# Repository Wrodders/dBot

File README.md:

# Two Wheel Self Balancing Mobile Robot

Final Year Capstone Mechatronics Project. 
Designed to be a cost effective platform for research and development of autonomous 
mobile robotics. The non linear and unstable dynamics of the Two Wheel Self Balancing Mobile Robot (TWSBMR)
make it a challenging platform for control and navigation.

Low Level motor control implemented on STM32F411RE microcontroller, using LibOpenCM3.
High Level Monocular Navigation uses RaspberryPi 5 with the Pi Camera V3.
[ComsTerm](https://github.com/Wrodders/ComsTerm) used as engineering UI. 

## Design

The project was built around milestones of autonomy:

* Stabilization
* Positional Control
* Teleoperation
* Path Following 
* Path Recovery 
* Track Racing

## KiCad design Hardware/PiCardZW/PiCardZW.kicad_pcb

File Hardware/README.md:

# STM32 Black Pill Connection Diagram

```mermaid
graph TB
  subgraph STM32F401
    USART2 -->|PA2/3| Debug/Prog
    USART1 -->|PB6/7| Bluetooth
    TIMER3 -->|PA6/7 PB0/1| PWM
    TIMER1 -->|PA8/9/10/11| Encoder
    I2C1 --> |PB8/9| MPU6050
  end
```

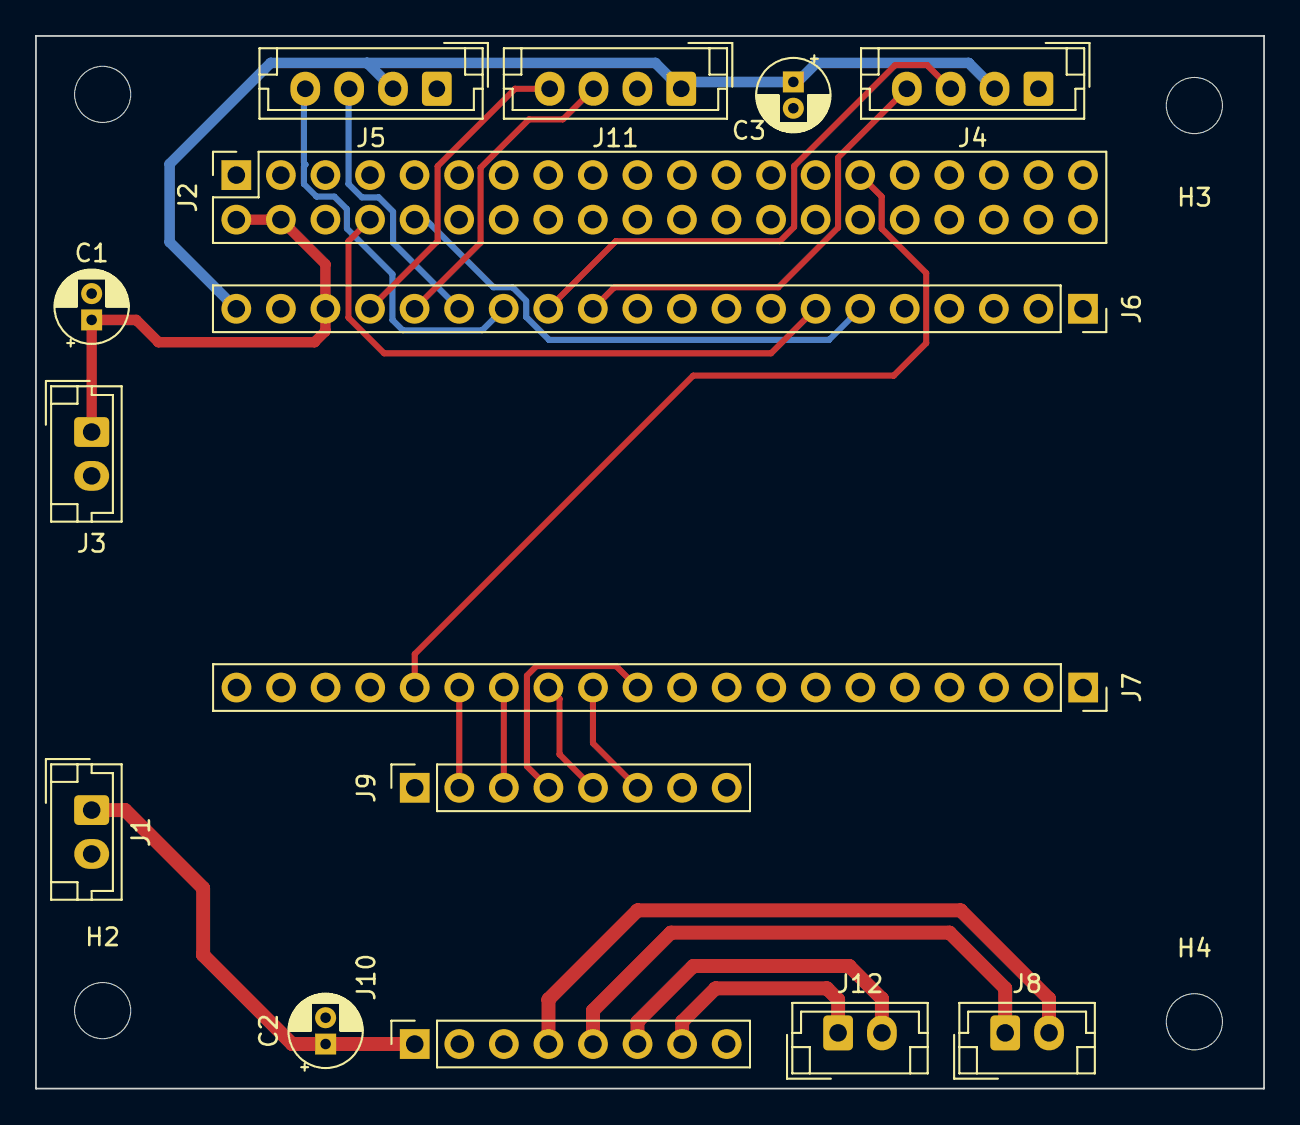
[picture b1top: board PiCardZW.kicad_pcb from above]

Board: 2 copper layers, 70.0 x 60.0 mm, 19 parts (0 on the bottom side), 22 nets.

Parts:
C1, C3: 10u; CP_Radial_D4.0mm_P1.50mm
C2: 100u; CP_Radial_D4.0mm_P1.50mm
H1, H2, H3, H4: MountingHole; MountingHole_3.2mm_M3
J1, J8, J12: Screw_Terminal_01x02; JST_EH_B2B-EH-A_1x02_P2.50mm_Vertical
J2: Conn_02x20_Odd_Even; PinSocket_2x20_P2.54mm_Vertical
J3: Conn_01x02; JST_EH_B2B-EH-A_1x02_P2.50mm_Vertical
J4, J5, J11: Conn_01x04; JST_EH_B4B-EH-A_1x04_P2.50mm_Vertical
J6, J7: Conn_01x20; PinSocket_1x20_P2.54mm_Vertical
J9, J10: Conn_01x08; PinSocket_1x08_P2.54mm_Vertical

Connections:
+3.3V: C3.1, J4.2, J5.2, J6.20, J7.3, J11.1
+5V: C1.1, J2.2, J2.4, J3.1, J6.18, J7.1
AOUT1: J8.2, J10.4
AOUT2: J8.1, J10.5
BOUT1: J10.6, J12.2
BOUT2: J10.7, J12.1
DEBUG_RX: J2.8, J6.7
DEBUG_TX: J2.10, J6.6
DRV_EN: J7.11, J9.4
ENCL_A: J4.4, J6.12
ENCL_B: J4.3, J6.13
ENCR_A: J5.4, J6.14
ENCR_B: J5.3, J6.15
GND: C1.2, C2.2, C3.2, J1.2, J2.6, J2.9, J2.14, J2.20, J2.25, J2.30, J2.34, J2.39, J3.2, J4.1, J5.1, J6.19, J7.2, J9.8, J10.3, J10.8, J11.2
IMU_SCL: J6.16, J11.3
IMU_SDA: J6.17, J11.4
ML_PWMA: J7.15, J9.2
ML_PWMB: J7.14, J9.3
MR_PWMA: J7.13, J9.5
MR_PWMB: J7.12, J9.6
VM: C2.1, J1.1, J10.1
nRST: J2.29, J7.16

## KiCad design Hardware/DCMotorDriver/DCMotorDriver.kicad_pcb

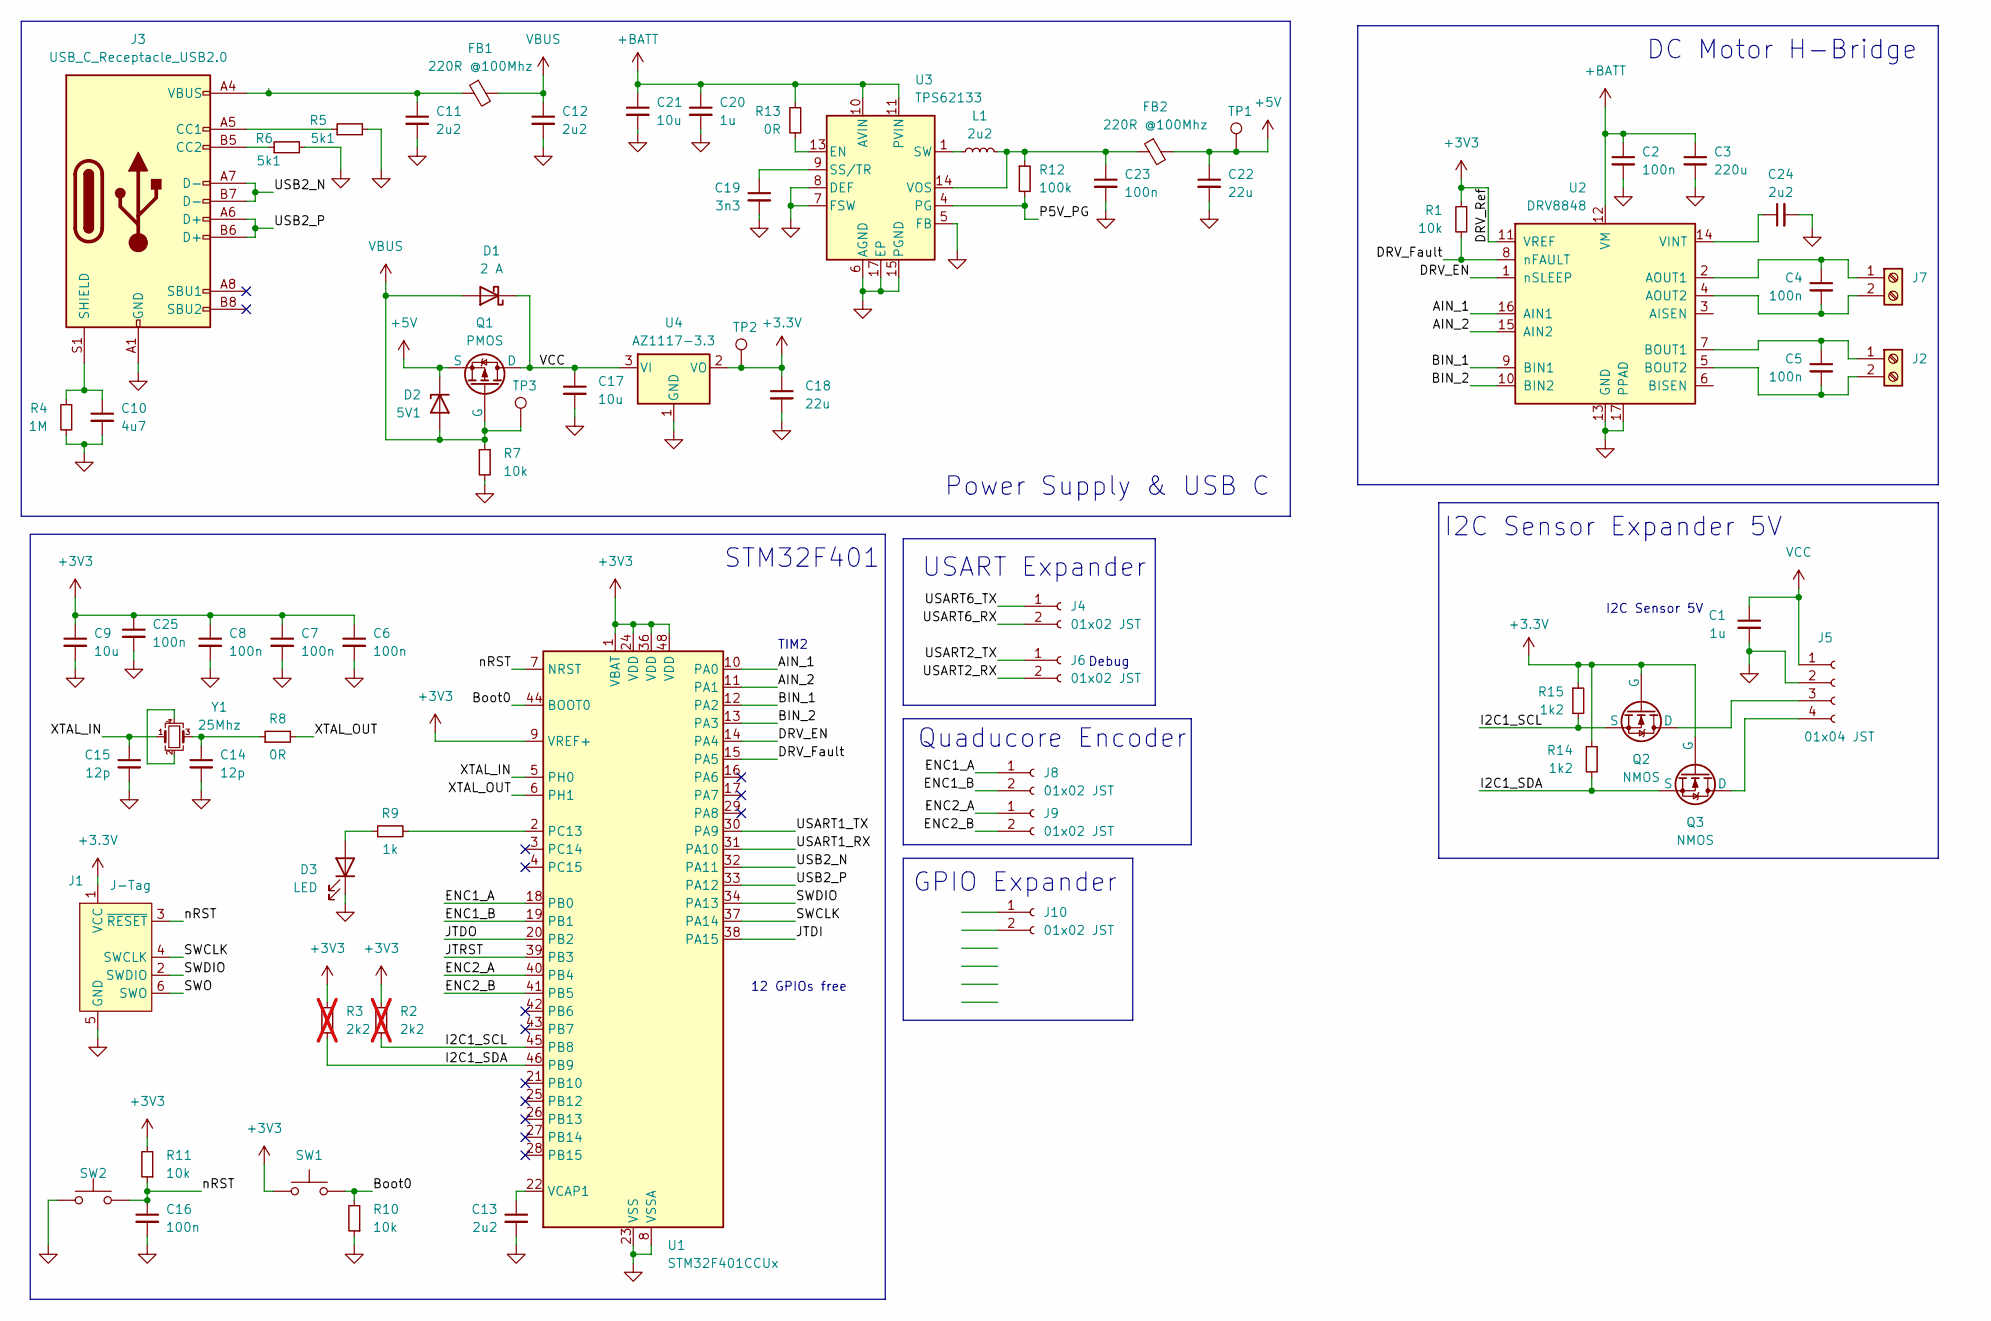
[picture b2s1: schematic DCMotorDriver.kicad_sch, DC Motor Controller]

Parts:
C1, C20: 1u; C_0402_1005Metric
C2, C4, C5, C6, C7, C8, C16, C23, C25: 100n; C_0402_1005Metric
C3: 220u; C_0402_1005Metric
C9, C17, C21: 10u; C_0402_1005Metric
C10: 4u7; C_0402_1005Metric
C11, C12, C13, C24: 2u2; C_0402_1005Metric
C14, C15: 12p; C_0402_1005Metric
C18, C22: 22u; C_0402_1005Metric
C19: 3n3; C_0402_1005Metric
D1: 2 A; D_0603_1608Metric
D2: 5V1; D_0402_1005Metric
D3: LED; D_0402_1005Metric
FB1, FB2: 220R @100Mhz; L_0402_1005Metric
J1: J-Tag; Tag-Connect_TC2030-IDC-FP_2x03_P1.27mm_Vertical
J2, J7: Screw_Terminal_01x02; PinHeader_1x02_P2.54mm_Horizontal
J3: USB_C_Receptacle_USB2.0; USB_C_Receptacle_XKB_U262-16XN-4BVC11
J4, J6, J8, J9, J10: 01x02 JST; JST_EH_B2B-EH-A_1x02_P2.50mm_Vertical
J5: 01x04 JST; JST_EH_B4B-EH-A_1x04_P2.50mm_Vertical
L1: 2u2; L_0805_2012Metric
Q1: PMOS; SOT-23-3
Q2, Q3: NMOS; SOT-23-3
R1, R7, R10, R11: 10k; R_0402_1005Metric
R2, R3: 2k2; R_0402_1005Metric; not fitted
R4: 1M; R_0402_1005Metric
R5, R6: 5k1; R_0402_1005Metric
R8, R13: 0R; R_0402_1005Metric
R9: 1k; R_0402_1005Metric
R12: 100k; R_0402_1005Metric
R14, R15: 1k2; R_0402_1005Metric
SW1, SW2: SW_Push; SW_Push_1P1T_NO_CK_KMR2
TP1, TP2, TP3: TestPoint; TestPoint_Pad_D1.0mm
U1: STM32F401CCUx; QFN-48-1EP_7x7mm_P0.5mm_EP5.6x5.6mm
U2: DRV8848; TSSOP-16-1EP_4.4x5mm_P0.65mm
U3: TPS62133; VQFN-16-1EP_3x3mm_P0.5mm_EP1.68x1.68mm_ThermalVias
U4: AZ1117-3.3; SOT-223-3_TabPin2
Y1: 25Mhz; Crystal_SMD_0603-4Pin_6.0x3.5mm

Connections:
+3.3V: C18.1, J1.1 (VCC), Q2.2 (G), Q3.2 (G), R14.1, R15.1, TP2.1, U4.2 (VO)
+3V3: C6.1, C7.1, C8.1, C9.1, C25.1, R1.1, R2.1, R3.1, R11.2, SW1.1, U1.1 (VBAT), U1.9 (VREF+), U1.24 (VDD), U1.36 (VDD), U1.48 (VDD), U2.11 (VREF)
+5V: C22.1, D2.1 (K), FB2.2, Q1.3 (S), TP1.1
+BATT: C2.1, C3.1, C20.1, C21.1, R13.1, U2.12 (VM), U3.10 (AVIN), U3.11 (PVIN), U3.12 (PVIN)
/AIN_1: U1.10 (PA0), U2.16 (AIN1)
/AIN_2: U1.11 (PA1), U2.15 (AIN2)
/BIN_1: U1.12 (PA2), U2.9 (BIN1)
/BIN_2: U1.13 (PA3), U2.10 (BIN2)
/Boot0: R10.2, SW1.2, U1.44 (BOOT0)
/DRV_EN: U1.14 (PA4), U2.1 (nSLEEP)
/DRV_Fault: R1.2, U1.15 (PA5), U2.8 (nFAULT)
/ENC1_A: J8.1, U1.18 (PB0)
/ENC1_B: J8.2, U1.19 (PB1)
/ENC2_A: J9.1, U1.40 (PB4)
/ENC2_B: J9.2, U1.41 (PB5)
/I2C1_SCL: Q2.3 (S), R2.2, R15.2, U1.45 (PB8)
/I2C1_SDA: Q3.3 (S), R3.2, R14.2, U1.46 (PB9)
/JTDI: U1.38 (PA15)
/JTDO: U1.20 (PB2)
/JTRST: U1.39 (PB3)
/P5V_PG: R12.2, U3.4 (PG)
/SWCLK: J1.4 (SWCLK), U1.37 (PA14)
/SWDIO: J1.2 (SWDIO), U1.34 (PA13)
/SWO: J1.6 (SWO)
/USART1_RX: U1.31 (PA10)
/USART1_TX: U1.30 (PA9)
/USART2_RX: J6.2
/USART2_TX: J6.1
/USART6_RX: J4.2
/USART6_TX: J4.1
/USB2_N: J3.A7 (D-), J3.B7 (D-), U1.32 (PA11)
/USB2_P: J3.A6 (D+), J3.B6 (D+), U1.33 (PA12)
/XTAL_IN: C15.1, U1.5 (PH0), Y1.1
/XTAL_OUT: R8.2, U1.6 (PH1)
/nRST: C16.1, J1.3 (~RESET), R11.1, SW2.2, U1.7 (NRST)
GND: C1.2, C2.2, C3.2, C6.2, C7.2, C8.2, C9.2, C10.2, C11.2, C12.2, C13.2, C14.2, C15.2, C16.2, C17.2, C18.2, C19.2, C20.2, C21.2, C22.2, C23.2, C24.2, C25.2, D3.1 (K), J1.5 (GND), J3.A1 (GND), J3.A12 (GND), J3.B1 (GND), J3.B12 (GND), J5.2, R4.2, R5.2, R6.2, R7.2, R10.1, SW2.1, U1.8 (VSSA), U1.23 (VSS), U1.35 (VSS), U1.47 (VSS), U1.49 (VSS), U2.13 (GND), U2.17 (PPAD), U3.5 (FB), U3.6 (AGND), U3.7 (FSW), U3.8 (DEF), U3.15 (PGND), U3.16 (PGND), U3.17 (EP), U4.1 (GND)
unnamed: C11.1, FB1.1, J3.A4 (VBUS), J3.A9 (VBUS), J3.B4 (VBUS), J3.B9 (VBUS)
unnamed: C14.1, R8.1, Y1.3
unnamed: D3.2 (A), R9.1
unnamed: C5.1, J2.1, U2.7 (BOUT1)
unnamed: C5.2, J2.2, U2.5 (BOUT2)
unnamed: J3.A5 (CC1), R5.1
unnamed: J3.B5 (CC2), R6.1
unnamed: C10.1, J3.S1 (SHIELD), R4.1
unnamed: J5.3, Q2.1 (D)
unnamed: J5.4, Q3.1 (D)
unnamed: C4.1, J7.1, U2.2 (AOUT1)
unnamed: C4.2, J7.2, U2.4 (AOUT2)
unnamed: L1.1, U3.1 (SW), U3.2 (SW), U3.3 (SW)
unnamed: R9.2, U1.2 (PC13)
unnamed: C13.1, U1.22 (VCAP1)
unnamed: C24.1, U2.14 (VINT)
unnamed: R13.2, U3.13 (EN)
unnamed: C19.1, U3.9 (SS/TR)
unnamed: C23.1, FB2.1, L1.2, R12.1, U3.14 (VOS)
unnamed: Y1.2, Y1.4
VBUS: C12.1, D1.2 (A), D2.2 (A), FB1.2, Q1.2 (G), R7.1, TP3.1
VCC: C1.1, C17.1, D1.1 (K), J5.1, Q1.1 (D), U4.3 (VI)

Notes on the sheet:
I2C Sensor Expander 5V
Quaducore Encoder
12 GPIOs free
USART Expander
Power Supply & USB C
TIM2
Debug
DC Motor H-Bridge
I2C Sensor 5V
STM32F401
GPIO Expander

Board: 2 copper layers, 69 parts (0 on the bottom side), 48 nets, no tracks yet.

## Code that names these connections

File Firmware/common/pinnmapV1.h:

#ifndef PINMAPV1_H
#define PINMAPV1_H

#include <libopencm3/stm32/gpio.h>
// **************** PIN DEFINITIONS ********************** //
// Debug Led
#define LED_PORT 		GPIOC
#define LED_PIN			GPIO13
// Debug UART 
#define DEBUG_USART		USART1
#define DEBUG_PORT		GPIOA
#define DEBUG_RX		GPIO10 
#define DEBUG_TX		GPIO9
// Bluetooth UART
#define BT_USART		USART6
#define BT_PORT			GPIOA
#define BT_TX			GPIO11
#define BT_RX			GPIO12
// MPU6050 IMU
#define IMU_PERIF       I2C1
#define IMU_PORT		GPIOB 
#define IMU_SDA			GPIO9
#define IMU_SCL			GPIO8
// DRV8833 2-CH PWM DC Motor Driver 
#define M_L_TIM 	    TIM2    // Left Motor PWM Timer 32bit count 16bit prescaler
#define M_L_PORT	    GPIOA   // Left Motor PWM Port
#define M_L_PWMA        GPIO0   // Left Motor PWM CH1 Pin
#define M_L_PWMB	    GPIO1   // Left Motor PWM CH2 Pin

#define M_R_TIM		    TIM2    // Right Motor PWM Timer 
#define M_R_PORT	    GPIOA   // Right Motor PWM Port
#define M_R_PWMA		GPIO2   // Right Motor PWM CH3 Pin
#define M_R_PWMB		GPIO3   // Right Motor PWM CH4 Pin

#define DRV_EN_PIN      GPIO4   //  Enable PIN
#define DRV_EN_PORT     GPIOA   //  Enable PORT

#define DRV_MODE_PIN    GPIO15   //  DRV8876 Mode PIN
#define DRV_MODE_PORT   GPIOC    // DRV8876 Mode PORT


// 
// Quaducore Hall Effect Encoder
#define ENC_R_TIM       TIM3
#define ENC_R_AF        GPIO_AF2
#define ENC_R_PORT      GPIOB
#define ENC_R_A         GPIO4   // TIM3 CH1
#define ENC_R_B         GPIO5   // TIM3 CH2

#define ENC_L_TIM       TIM4
#define ENC_L_AF        GPIO_AF2
#define ENC_L_PORT      GPIOB
#define ENC_L_A         GPIO6   // TIM4 CH1
#define ENC_L_B         GPIO7   // TIM4 CH2

#endif // PINMAPV1_H

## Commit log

2023-11-02 initial
2023-11-02 BlinkyCM3
2023-11-02 HelloWorld
2023-11-02 uart TX IRQ
2023-11-02 timer PWM
2023-11-02 I2C Sensor test
2023-11-02 MPU6050 MADJWICK FILTER
2023-11-03 SerialZMQ
2023-11-05 Console
2023-11-05 Model Assembled
2023-11-05 V1 STL
2023-11-06 DC Driver SCH
2023-11-06 layout v1
2023-11-15 BUGFIX-SerialBlockRXdisconnected
2023-11-15 tempFix IMU iniAddr
2023-11-15 simplified cli
2023-11-16 sensorSimulator
2023-11-17 realtimePlot
2023-11-21 cleanup
2023-11-22 RX_IRQ
2023-11-22 TRX_RingBuf
2023-12-02 serialTesting
2023-12-02 ploter
2023-12-29 IMU Quaternion-Euler
2023-12-29 plotMsgFilter
2023-12-29 comsrequierements
2023-12-29 DCMotorDriver
2023-12-29 encoderInitial
2023-12-29 FIFOqueue
2023-12-29 addQueue
2023-12-31 tests
2023-12-31 hardwareRestart
2024-01-09 CheckpointIMU&SerialPass
2024-01-25 ComsTermV4
2024-01-25 serialReader
2024-01-25 complementaryFilter
2024-01-25 pcbProtoLayout
2024-01-25 restructure
2024-01-25 libserialport
2024-01-26 cUtilsmodule
2024-01-28 modules
2024-01-28 organising
2024-01-28 hardware
2024-01-28 Readme
2024-01-29 swPlan
2024-01-31 updatecUtils
2024-01-31 update submodules branch main
2024-02-02 multiple Serial RB Packets
2024-02-02 fix block recvBuff
2024-02-14 firmware
2024-02-14 software
2024-02-15 cleanMatalb
2024-02-15 DCMotorModel
2024-02-17 updateComsTerm
2024-02-21 fixBuild
2024-02-21 update modules
2024-02-27 matlab
2024-02-27 renaming
2024-02-27 imu LowPass
2024-02-27 cadV2
2024-02-27 motorPWM
2024-02-29 ddmr
2024-03-10 cleanUpStyle
2024-03-10 ddmrModel
2024-03-12 DC Motor PI
2024-03-13 verifRbUpdateSerial
2024-03-18 pubMsg & motorCleanup
2024-03-18 fixMotorDir
2024-03-18 fixBugs
2024-03-18 PIDTuneMatlab
2024-03-19 speedTuningV2
2024-03-20 chirpInitial
2024-03-20 chirpLib
2024-03-24 chirp
2024-03-24 diffDrive
2024-03-24 pidFix
2024-03-24 splitRobotDynamics
2024-03-25 balancePidInitial
2024-03-25 balanceRefactoreStash
2024-03-25 balanceRestructure
2024-03-25 balancePIDV2
2024-03-25 motorMin
2024-03-25 v2PintOut
2024-03-25 updateCAD
2024-03-26 ctrl
2024-03-28 v2MotorTest
2024-03-28 v2UpgradedTested
2024-03-28 ControlsUpdateMatlab
2024-03-28 piStmStream
2024-03-28 updateSubmodule
2024-03-28 desingDocs
2024-03-30 balancePTuned
2024-03-30 balanceTuned
2024-03-30 motionTuned
2024-03-30 batBalanceinitialtune
2024-04-04 Modeling
2024-04-04 fix motor bug
2024-04-04 motorPITunedV3
2024-04-04 fixMotorBuf
2024-04-17 v3Tune
2024-09-29 imuDriverUpdate
2024-10-15 Reorg
2024-10-23 HackyRXmsgComs
2024-10-23 cmdParseInitial
2024-10-26 2wayComsGETSET
2024-10-31 V1BALANCE
2024-11-12 mDriverV2
2024-11-17 paramLookup
2024-11-17 V1STEERCTRL
2024-11-17 refactor
2024-11-23 CamCalibrateInit
2024-11-23 method1
2024-11-24 method1V2
2024-11-28 file
2024-12-04 cMotroSerialDriver
2024-12-04 eeod
2024-12-06 StatePublihser
2024-12-07 FKBot
2024-12-12 Software Structure
2024-12-12 TunedVel
2024-12-12 Dynamics
2025-01-27 refactorSerComs
2025-01-27 twsbDriver-SelectIO
2025-01-27 twsb-testtedIO
2025-01-28 twsbdriver-zmqmTransmit
2025-01-28 letexBegin
2025-02-02 jumptodfu
2025-02-03 SerialOTAConsole
2025-02-04 twsbConsole
2025-02-04 twsbZMQCOMS
2025-02-05 serComsRestrucutre
2025-02-07 comsCmdVisionIntial
2025-02-08 VISION EDGE HIST
2025-02-08 FIXTWSBConsoleBug
2025-02-10 fixTWSBCOMS_pizeroinitbug
2025-02-10 bugtesting
2025-02-13 ongoingdev
2025-02-17 ongoing
2025-02-21 V2Bringup
2025-02-24 purging GenAI Drivel
2025-02-25 anotherday$
2025-02-25 visionPipeCleanUP
2025-02-25 visionServices
2025-02-27 reporteod
2025-03-02 retvalfmt
2025-03-04 dataCollection
2025-03-06 eodeod
2025-03-06 updateParams
2025-03-11 LineFollowWorking:)
2025-03-11 dataprocessing
2025-03-15 beod
2025-03-22 TopologicalPeakTracker
2025-03-22 dataRate
2025-03-23 pathFollwoSpeedModulate
2025-03-25 refactorVision
2025-04-02 bevCalibChessInitial
2025-04-02 bevCalibChess
2025-04-02 gryodometryInit
2025-04-03 bangbang
2025-04-04 postionTracking
2025-04-06 trackerslide
2025-04-06 effeicentTracker
2025-04-07 HighSpeedRateLimiterThrottle
2025-04-13 dissDone
2025-04-13 README.md
2025-04-13 updateiir
